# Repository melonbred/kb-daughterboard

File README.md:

# kb-daughterboard

## Introduction

This project is a USB-C daughterboard that provides with ESD protection and a standard 4-pin JST connector. Dimensions are approximately 42 x 11mm and has two M2 screw mounts. This daughterboard was heavily influenced by the [C3 Unified Daughterboard](https://github.com/ai03-2725/Unified-Daughterboard) project. While the C3 Unified Daughterboard is a great product, this daughterboard offers a different footprint and vertical JST connector.

## Features
Similarly to the Unified Daugherboard, this daughterboard features the following:
- Overcurrent protection through a PTC fuse
- Overvoltage protection through a TVS diode
- Single-path USB-C shield grounding to a metal chasis. ESD is disappited through a resistor and diode.

Please note that this daughterboard does not include resistors for the USB data lines which may be required for some microprocessors. If these resistors are required for your application, please provide them on the PCB mainboard.

There are also two versions of this daughterboard. One with the USB-C receptacle flush to the PCB; The other with the USB-C receptacle protruded out. Please see the .step files for reference.

## Production
Please note that the produection files were prepared with JLCPCB's SMT assembly in mind. Should you deicide to proceed with a different manufacturer, the Bill of Materials (BOM) and position files may need to be modified.

## Acknowledgment

This project was collaboration with [matthewdias](https://github.com/matthewdias).

As mentioned above, this project was heavily influenced by the [C3 Unified Daughterboard](https://github.com/ai03-2725/Unified-Daughterboard).

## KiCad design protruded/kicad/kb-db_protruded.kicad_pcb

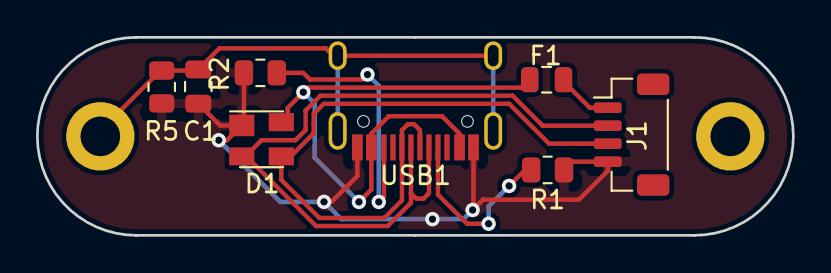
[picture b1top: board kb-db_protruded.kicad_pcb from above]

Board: 2 copper layers, 42.0 x 11.0 mm, 10 parts (0 on the bottom side), 8 nets.

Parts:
C1: 4.7n; C_0805_2012Metric
D1: PRTR5V0U2X; SOT-143
F1: 500mA; Fuse_0805_2012Metric
H1, H2: MountingHole_Pad; MountingHole_2.2mm_M2_DIN965_Pad
J1: Conn_01x04; JST_SH_BM04B-SRSS-TB_1x04-1MP_P1.00mm_Vertical
R1, R2: 5.1k; R_0805_2012Metric
R5: 1M; R_0805_2012Metric
USB1: HRO-TYPE-C-31-M-12; HRO-TYPE-C-31-M-12-Assembly

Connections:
+5V: F1.1, J1.1
D+: D1.3, J1.3, USB1.6, USB1.8
D-: D1.2, J1.2, USB1.5, USB1.7
Earth: C1.1, H2.1, R5.1, USB1.13
GND: C1.2, D1.1, J1.4, R1.1, R2.1, R5.2, USB1.1, USB1.12
unnamed: R1.2, USB1.4
unnamed: R2.2, USB1.10
VCC: D1.4, F1.2, USB1.2, USB1.11

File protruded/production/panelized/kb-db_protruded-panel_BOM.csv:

Designator,Footprint,Quantity,Value,LCSC Part #
"D1,D1",SOT-143,2,PRTR5V0U2X,C2827688
"R2,R1,R2,R1",R_0805_2012Metric,4,5.1k,C26023
"F1,F1",Fuse_0805_2012Metric,2,500mA,C70076
"C1,C1",C_0805_2012Metric,2,4.7n,C541501
"J1,J1",JST_SH_BM04B-SRSS-TB_1x04-1MP_P1.00mm_Vertical,2,Conn_01x04,C160390
"USB1,USB1",HRO-TYPE-C-31-M-12-Assembly,2,HRO-TYPE-C-31-M-12,C167321
"R5,R5",R_0805_2012Metric,2,1M,C325768

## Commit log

2021-04-26 Added pcb render
2021-04-26 Cleaned up unecessary footprints
2021-04-26 Add submodules
2021-04-26 Added image
2021-04-26 Added step
2021-05-03 Added production data
2021-05-03 Updated cpl
2022-01-15 Ground components to USB ground
2022-01-18 update image
2022-01-22 added protruded version. file management
2022-01-22 Update Images
